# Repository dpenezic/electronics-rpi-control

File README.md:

# Wireless Control for the Raspberry Pi

## Description
This is a simple Hat that enables wireless control of the Raspberry Pi.

## Images

##Main features:
- Wireless control using ESP8266-07 module
- 5v input voltage from external socket 
- 5v and 3v3 power led indicators
- Four general purpose leds
- Easy access to ESP8266-07 GPIOs 
- ESP8266-07 programming button

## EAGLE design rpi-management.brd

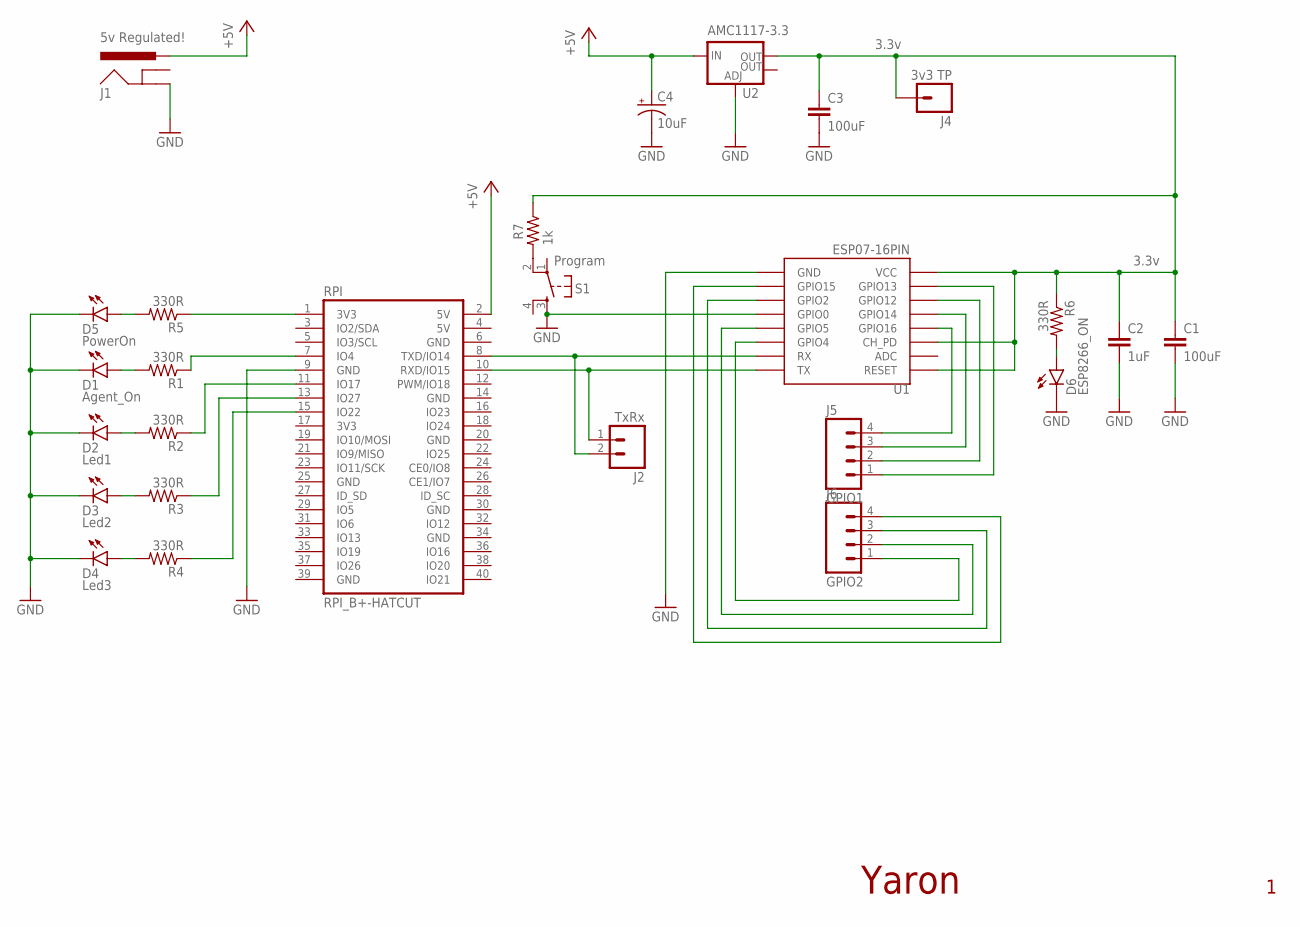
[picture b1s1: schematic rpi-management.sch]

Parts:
C1, C3: 100uF; 0603-CAP
C2: 1uF; 0603-CAP
C4: 10uF; EIA6032
D1: Agent_On; LED-0603
D2: Led1; LED-0603
D3: Led2; LED-0603
D4: Led3; LED-0603
D5: PowerOn; LED-0603
D6: ESP8266_ON; LED-0603
J1: 5v Regulated!; POWER_JACK_SLOT
J2: TxRx; 1X02
J4: 3v3 TP; 1X01
J5: GPIO1; 1X04
J6: GPIO2; 1X04
R1, R2, R3, R4, R5, R6: 330R; 0603-RES
R7: 1k; 0603-RES
RPI: RPI_B+-HATCUT; RPI-B+HAT_CUTOUT
S1: Program; TACTILE-PTH
U1: ESP07-16PIN
U2: AMC1117-3.3; SOT223

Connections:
+5V: C4.P$1 (+), J1.PWR, RPI.2 (5V), U2.3 (IN)
GND: C1.2, C2.2, C3.2, C4.P$2 (-), D1.C, D2.C, D3.C, D4.C, D5.C, D6.C, J1.GND@2 (GND), RPI.9 (GND), S1.3, U1.GND, U1.GPIO0, U2.1 (ADJ)
unnamed: D1.A, R1.2
unnamed: D2.A, R2.2
unnamed: D3.A, R3.2
unnamed: D4.A, R4.2
unnamed: D5.A, R5.2
unnamed: R1.1, RPI.7 (IO4)
unnamed: R2.1, RPI.11 (IO17)
unnamed: R3.1, RPI.13 (IO27)
unnamed: R4.1, RPI.15 (IO22)
unnamed: R5.1, RPI.1 (3V3)
unnamed: J2.1, RPI.10 (RXD/IO15), U1.TX
unnamed: J2.2, RPI.8 (TXD/IO14), U1.RX
unnamed: R7.2, S1.2
unnamed: J5.4, U1.GPIO16
unnamed: D6.A, R6.2
unnamed: C1.1, C2.1, C3.1, J4.1, R6.1, R7.1, U1.CH_PD, U1.REST (RESET), U1.VCC, U2.2 (OUT)
unnamed: J5.3, U1.GPIO14
unnamed: J5.2, U1.GPIO12
unnamed: J5.1, U1.GPIO13
unnamed: J6.1, U1.GPIO4
unnamed: J6.3, U1.GPIO2
unnamed: J6.4, U1.GPIO15
unnamed: J6.2, U1.GPIO5

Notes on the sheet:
3.3v
Yaron

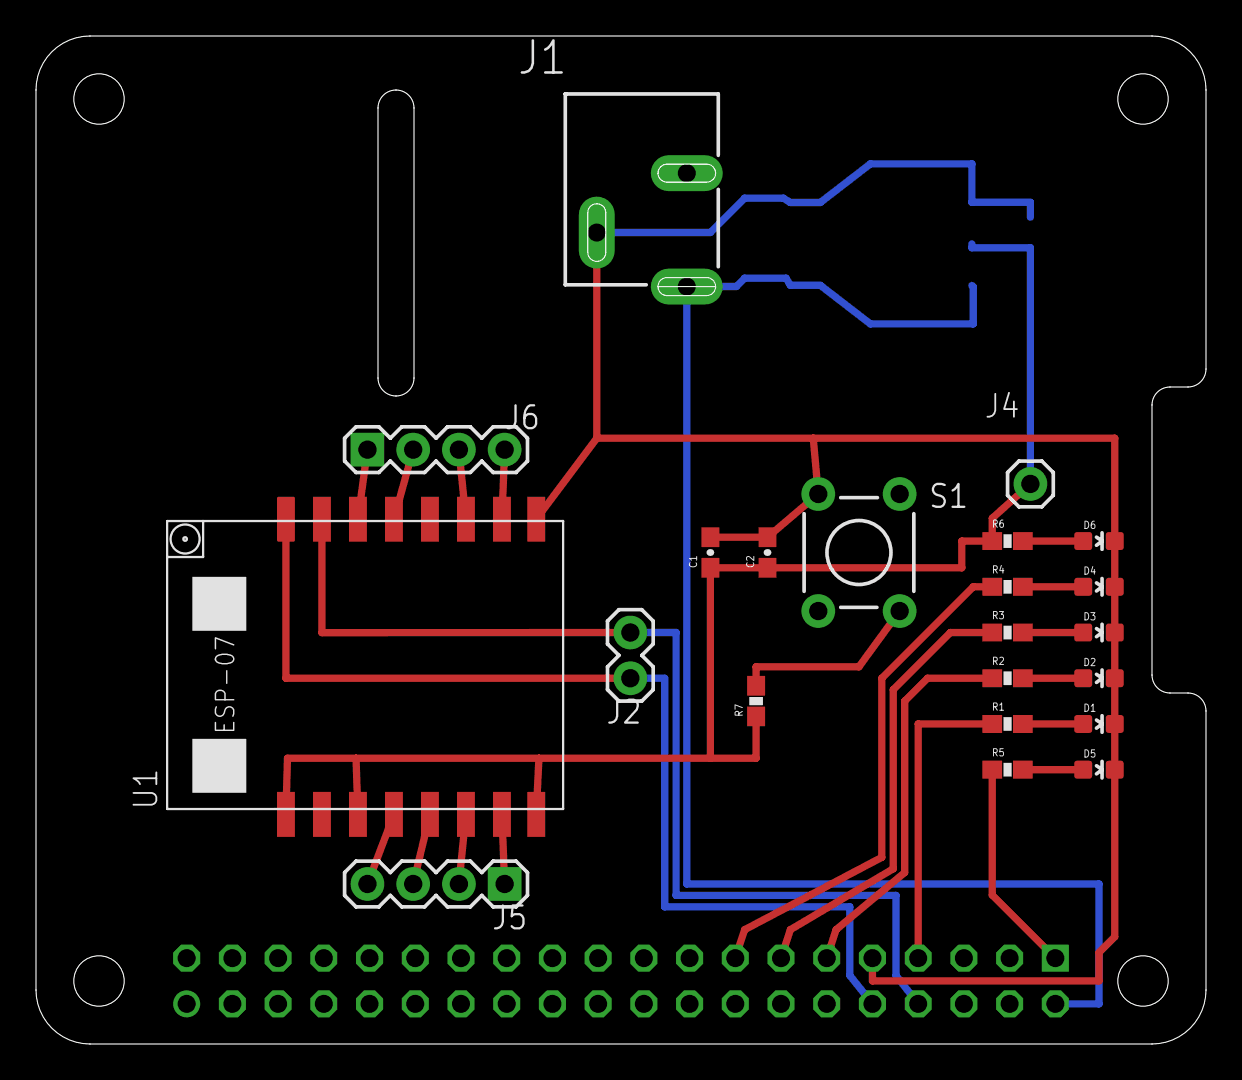
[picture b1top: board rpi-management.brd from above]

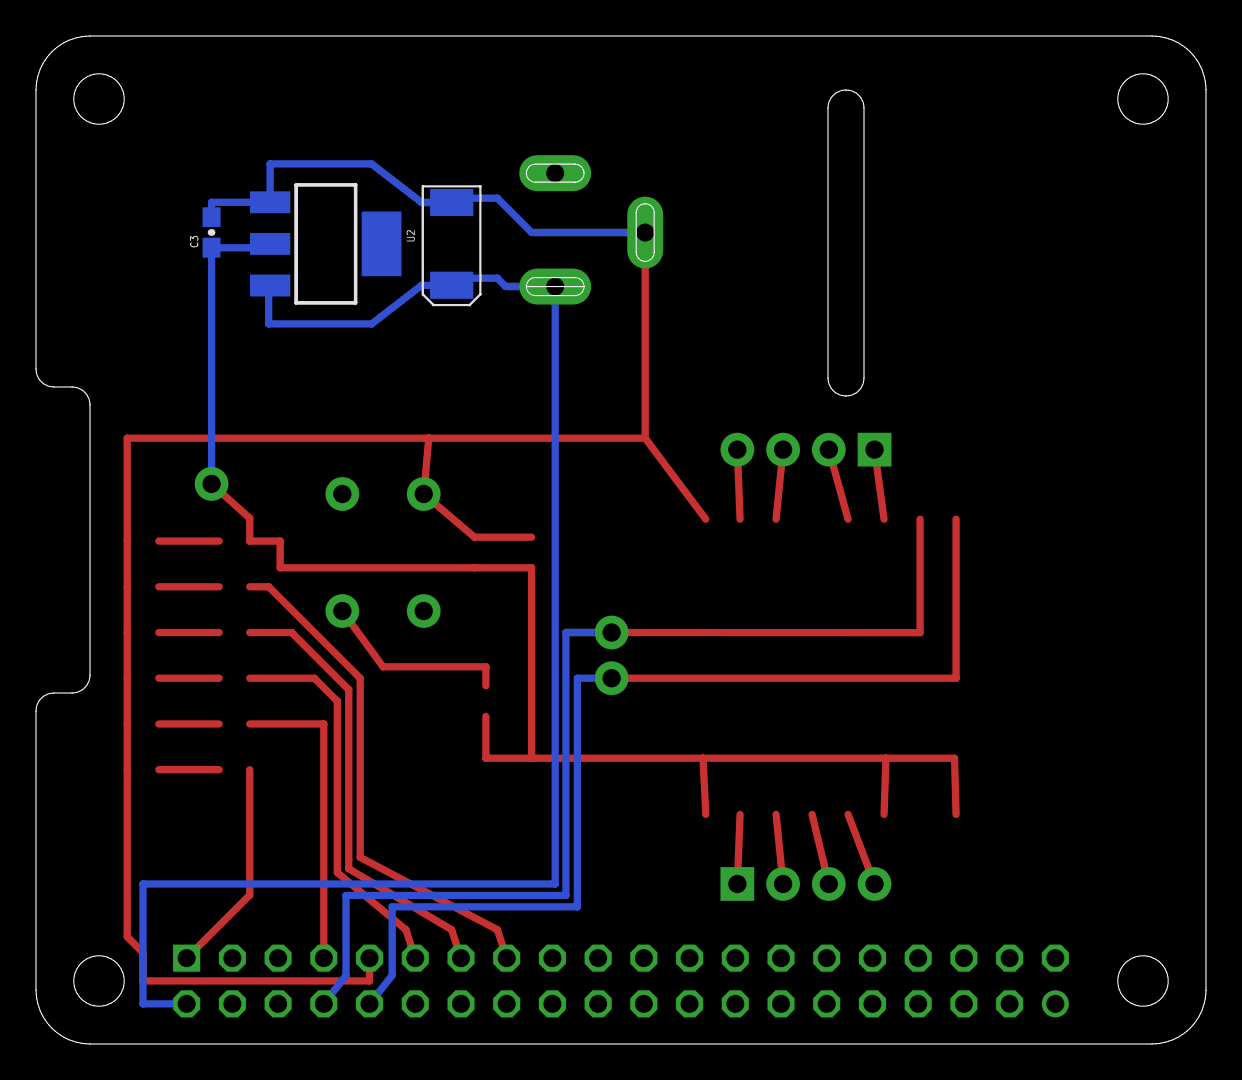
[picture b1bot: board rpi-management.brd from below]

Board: 2 copper layers, 65.0 x 56.0 mm, 26 parts (3 on the bottom side), 25 nets.

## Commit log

2016-03-22 Added files via upload
2016-03-22 Added image
2016-03-22 Fixed folder structure
2016-03-22 Added PCB image

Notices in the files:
parts and their libraries:
SparkFun-Connectors: Licensing: Creative Commons ShareAlike 4.0 International - https://creativecommons.org/licenses/by-sa/4.0
